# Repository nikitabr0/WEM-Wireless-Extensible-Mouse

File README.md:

# WEM-Wireless-Extensible-Mouse
A computer mouse, that can be connected via USB-C, Bluetooth or a 2.GHz USB dongle. It will have some additional buttons and extra GPIO header(s) for adding more functionality later on.

## Licensing

- **Firmware:** Licensed under the MIT License — see `LICENSE.firmware`.
- **Hardware:** Licensed under CERN-OHL-P-V2 (Permissive) — see https://cern.ch/cern-ohl and `LICENSE.hardware`.

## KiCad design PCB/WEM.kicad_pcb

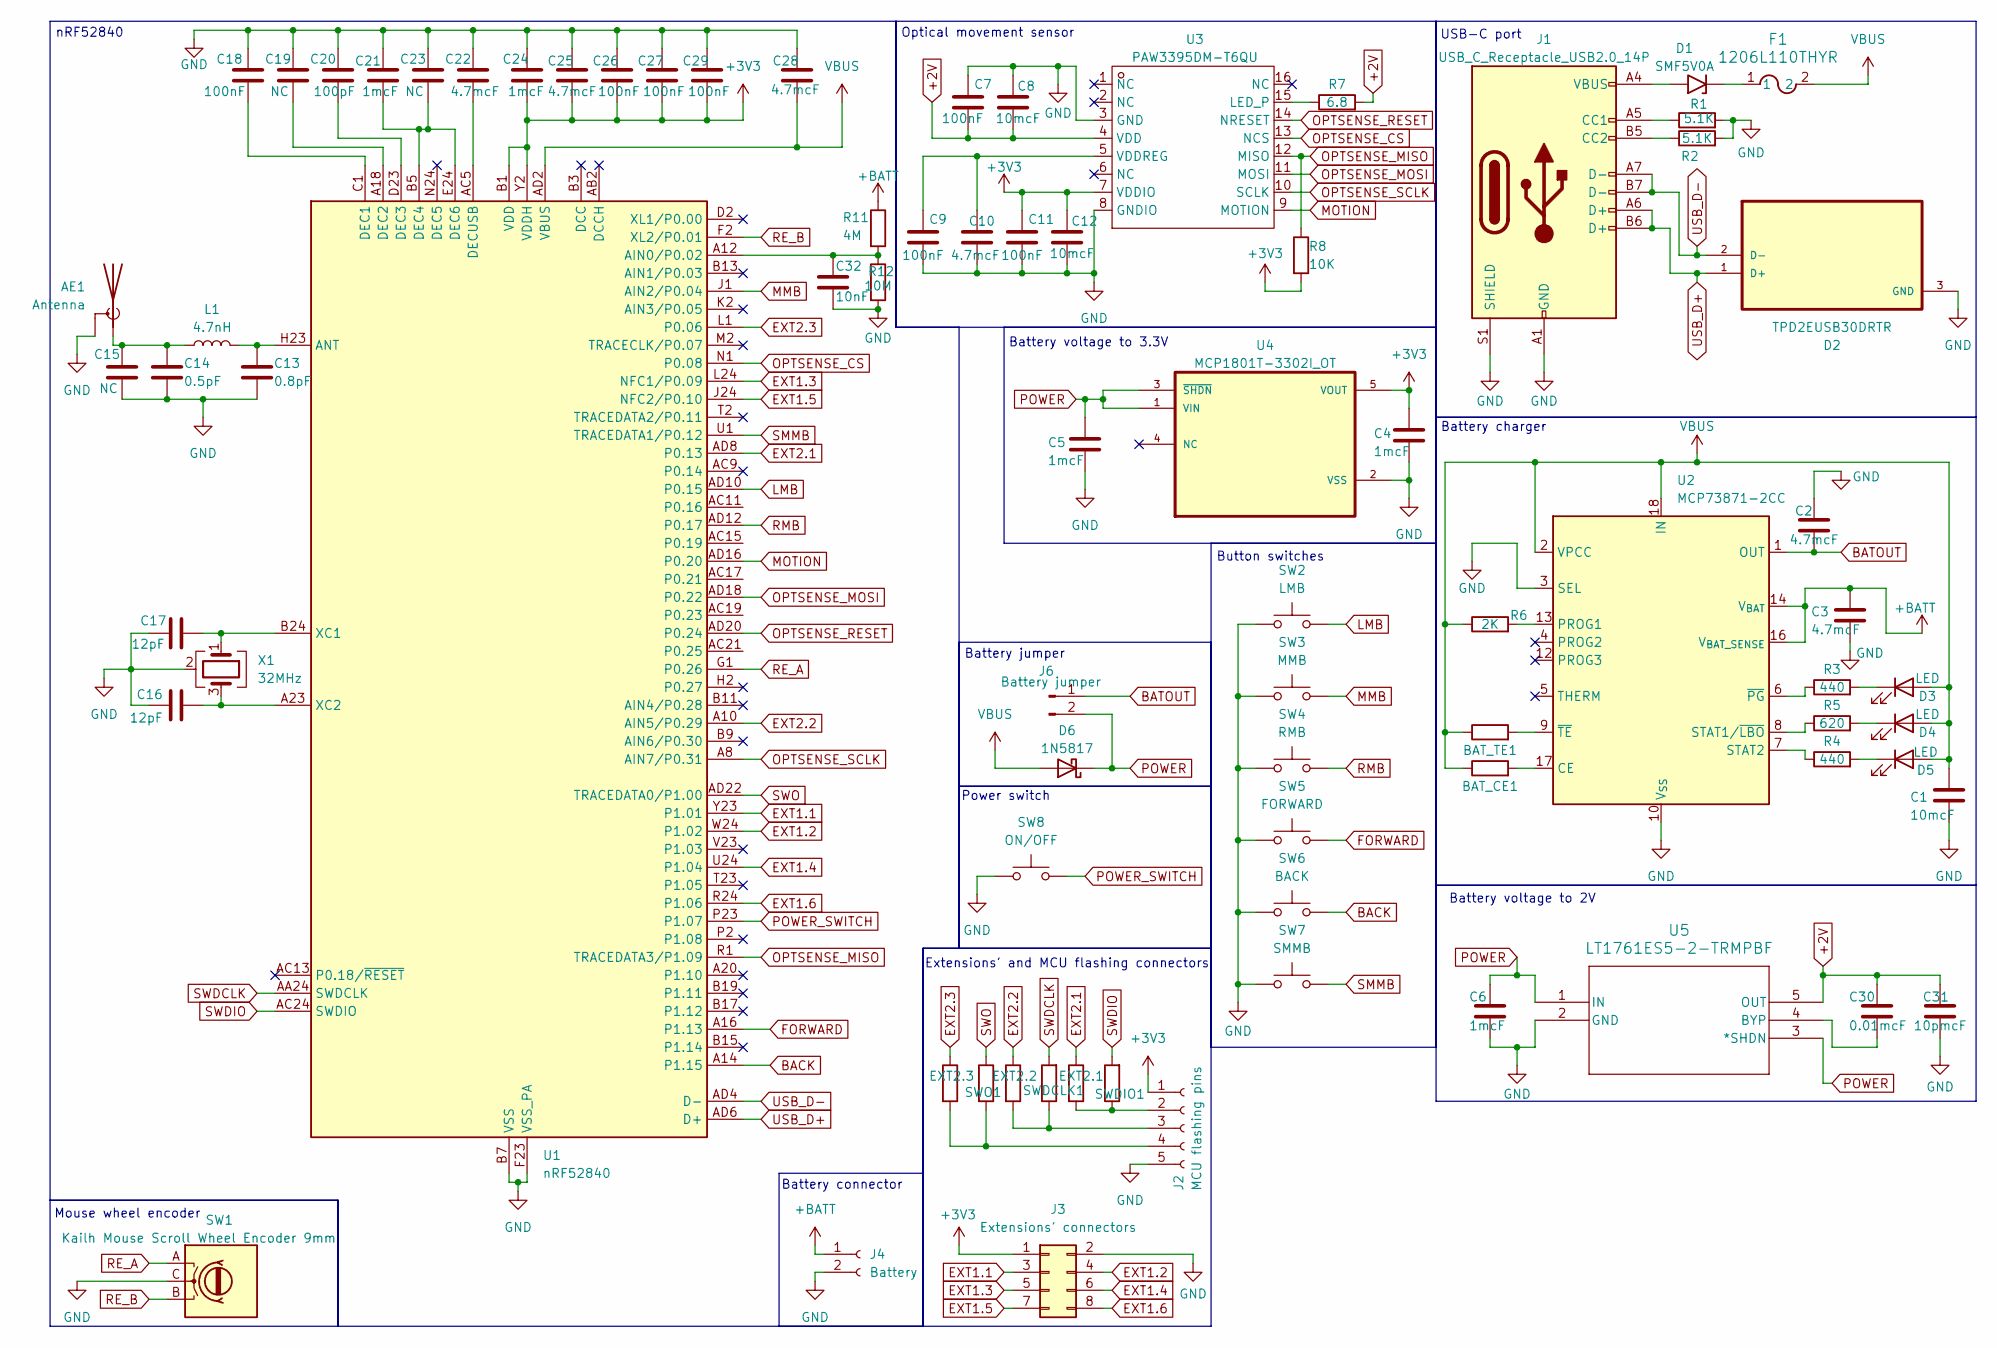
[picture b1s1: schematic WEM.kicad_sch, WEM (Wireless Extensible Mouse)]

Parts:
AE1: Antenna; Texas_SWRA117D_2.4GHz_Right
BAT_CE1: 0; R_0805_2012Metric_Pad1.20x1.40mm_HandSolder
BAT_TE1: 0; R_0805_2012Metric_Pad1.20x1.40mm_HandSolder
C1, C8, C12: 10mcF; C_0805_2012Metric_Pad1.18x1.45mm_HandSolder
C2, C3, C10: 4.7mcF; C_0805_2012Metric_Pad1.18x1.45mm_HandSolder
C4, C5, C6: 1mcF; C_0805_2012Metric_Pad1.18x1.45mm_HandSolder
C7, C9, C11: 100nF; C_0805_2012Metric_Pad1.18x1.45mm_HandSolder
C13: 0.8pF; C_0603_1608Metric_Pad1.08x0.95mm_HandSolder
C14: 0.5pF; C_0603_1608Metric_Pad1.08x0.95mm_HandSolder
C15, C19, C23: NC; C_0603_1608Metric_Pad1.08x0.95mm_HandSolder
C16, C17: 12pF; C_0603_1608Metric_Pad1.08x0.95mm_HandSolder
C18, C26, C27, C29: 100nF; C_0603_1608Metric_Pad1.08x0.95mm_HandSolder
C20: 100pF; C_0603_1608Metric_Pad1.08x0.95mm_HandSolder
C21, C24: 1mcF; C_0603_1608Metric_Pad1.08x0.95mm_HandSolder
C22, C25, C28: 4.7mcF; C_0603_1608Metric_Pad1.08x0.95mm_HandSolder
C30: 0.01mcF; C_0805_2012Metric_Pad1.18x1.45mm_HandSolder
C31: 10pmcF; C_0805_2012Metric_Pad1.18x1.45mm_HandSolder
C32: 10nF; C_0805_2012Metric_Pad1.18x1.45mm_HandSolder
D1: SMF5V0A; D_SMF
D2: TPD2EUSB30DRTR; SOTFL35P100X50-3N
D3, D4, D5: LED; LED_0805_2012Metric_Pad1.15x1.40mm_HandSolder
D6: 1N5817; D_SOD-323F
EXT2.1, EXT2.2, EXT2.3: 0; R_0805_2012Metric_Pad1.20x1.40mm_HandSolder
F1: 1206L110THYR; Fuse_1206_3216Metric_Pad1.42x1.75mm_HandSolder
J1: USB_C_Receptacle_USB2.0_14P; USB_C_Receptacle_GCT_USB4085
J2: MCU flashing pins; PinSocket_1x05_P2.54mm_Vertical
J3: Extensions' connectors; PinSocket_2x04_P2.54mm_Vertical
J4: Battery; JST_XH_B2B-XH-A_1x02_P2.50mm_Vertical
J6: Battery jumper; PinHeader_1x02_P2.54mm_Vertical
L1: 4.7nH; L_0402_1005Metric_Pad0.77x0.64mm_HandSolder
R1, R2: 5.1K; R_0805_2012Metric_Pad1.20x1.40mm_HandSolder
R3, R4: 440; R_0805_2012Metric_Pad1.20x1.40mm_HandSolder
R5: 620; R_0805_2012Metric_Pad1.20x1.40mm_HandSolder
R6: 2K; R_0805_2012Metric_Pad1.20x1.40mm_HandSolder
R7: 6.8; R_0805_2012Metric_Pad1.20x1.40mm_HandSolder
R8: 10K; R_0805_2012Metric_Pad1.20x1.40mm_HandSolder
R11: 4M; R_0805_2012Metric_Pad1.20x1.40mm_HandSolder
R12: 10M; R_0805_2012Metric_Pad1.20x1.40mm_HandSolder
SW1: Kailh Mouse Scroll Wheel Encoder 9mm
SW2: LMB; Kailh MI627301D07
SW3: MMB; Kailh MI627301D07
SW4: RMB; Kailh MI627301D07
SW5: FORWARD; Kailh MI627301D07
SW6: BACK; Kailh MI627301D07
SW7: SMMB; Kailh MI627301D07
SW8: ON/OFF; Kailh MI627301D07
SWDCLK1: 0; R_0805_2012Metric_Pad1.20x1.40mm_HandSolder
SWDIO1: 0; R_0805_2012Metric_Pad1.20x1.40mm_HandSolder
SWO1: 0; R_0805_2012Metric_Pad1.20x1.40mm_HandSolder
U1: nRF52840; Nordic_AQFN-73-1EP_7x7mm_P0.5mm
U2: MCP73871-2CC; QFN-20-1EP_4x4mm_P0.5mm_EP2.5x2.5mm
U3: PAW3395DM-T6QU; DIP-16_PAW3395DM-T6QU; Manufacturer Part PAW3395DM-T6QU; LCSC Part Name PAW3395DM-T6QU
U4: MCP1801T-3302I_OT; SOT-23-5_MC_MCH-M
U5: LT1761ES5-2-TRMPBF; S_5_ADI
X1: 32MHz; Crystal_SMD_2016-4Pin_2.0x1.6mm

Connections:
+2V: C7.2, C8.2, C30.1, C31.1, R7.2, U3.4 (VDD), U5.5 (OUT)
+3V3: C4.1, C11.1, C12.1, C24.2, C25.2, C26.2, C27.2, C29.2, J2.1, J3.1, R8.2, U1.A22 (VDD), U1.AD14 (VDD), U1.AD23 (VDD), U1.B1 (VDD), U1.W1 (VDD), U1.Y2 (VDDH), U3.7 (VDDIO), U4.5 (VOUT)
+BATT: C3.2, J4.1, R11.1, U2.14 (V_{BAT}), U2.15 (V_{BAT}), U2.16 (V_{BAT_SENSE})
BACK: SW6.2, U1.A14 (P1.15)
BATOUT: C2.1, J6.1, U2.1 (OUT), U2.20 (OUT)
EXT1.1: J3.3, U1.Y23 (P1.01)
EXT1.2: J3.4, U1.W24 (P1.02)
EXT1.3: J3.5, U1.L24 (NFC1/P0.09)
EXT1.4: J3.6, U1.U24 (P1.04)
EXT1.5: J3.7, U1.J24 (NFC2/P0.10)
EXT1.6: J3.8, U1.R24 (P1.06)
EXT2.1: EXT2.1.1, U1.AD8 (P0.13)
EXT2.2: EXT2.2.1, U1.A10 (AIN5/P0.29)
EXT2.3: EXT2.3.1, U1.L1 (P0.06)
FORWARD: SW5.2, U1.A16 (P1.13)
GND: AE1.2 (Shield), C1.2, C2.2, C3.1, C4.2, C5.2, C6.2, C7.1, C8.1, C9.2, C10.2, C11.2, C12.2, C13.2, C14.2, C15.2, C16.1, C17.1, C18.1, C19.1, C20.1, C21.1, C22.1, C23.1, C24.1, C25.1, C26.1, C27.1, C28.1, C29.1, C31.2, C32.2, D2.3 (GND), J1.A1 (GND), J1.A12 (GND), J1.B1 (GND), J1.B12 (GND), J1.S1 (SHIELD), J2.5, J3.2, J4.2, R1.2, R2.2, R12.2, SW1.C, SW2.1, SW3.1, SW4.1, SW5.1, SW6.1, SW7.1, SW8.1, U1.B7 (VSS), U1.EP (VSS), U1.F23 (VSS_PA), U2.3 (SEL), U2.10 (V_{SS}), U2.11 (V_{SS}), U2.21 (V_{SS}), U3.3 (GND), U3.8 (GNDIO), U4.2 (VSS), U5.2 (GND), X1.2 (G), X1.4 (G)
LMB: SW2.2, U1.AD10 (P0.15)
MMB: SW3.2, U1.J1 (AIN2/P0.04)
MOTION: U1.AD16 (P0.20), U3.9 (MOTION)
unnamed: AE1.1 (A), C14.1, C15.1, L1.1
unnamed: D1.1 (A1), F1.1
unnamed: D1.2 (A2), J1.A4 (VBUS), J1.A9 (VBUS), J1.B4 (VBUS), J1.B9 (VBUS)
unnamed: D3.1 (K), R3.2
unnamed: D4.1 (K), R5.2
unnamed: D5.1 (K), R4.2
unnamed: J1.A5 (CC1), R1.1
unnamed: J1.B5 (CC2), R2.1
unnamed: EXT2.1.2, J2.2, SWDIO1.1
unnamed: EXT2.2.2, J2.3, SWDCLK1.1
unnamed: EXT2.3.2, J2.4, SWO1.2
unnamed: C32.1, R11.2, R12.1, U1.A12 (AIN0/P0.02)
unnamed: C13.1, L1.2, U1.H23 (ANT)
unnamed: C18.2, U1.C1 (DEC1)
unnamed: C19.2, U1.A18 (DEC2)
unnamed: C20.2, U1.D23 (DEC3)
unnamed: C21.2, C23.2, U1.B5 (DEC4), U1.E24 (DEC6)
unnamed: C22.2, U1.AC5 (DECUSB)
unnamed: C17.2, U1.B24 (XC1), X1.1
unnamed: C16.2, U1.A23 (XC2), X1.3
unnamed: BAT_CE1.2, U2.17 (CE)
unnamed: R6.2, U2.13 (PROG1)
unnamed: R5.1, U2.8 (STAT1/~LBO)
unnamed: R4.1, U2.7 (STAT2)
unnamed: R3.1, U2.6 (~PG)
unnamed: BAT_TE1.2, U2.9 (~TE)
unnamed: R7.1, U3.15 (LED_P)
unnamed: C9.1, C10.1, U3.5 (VDDREG)
unnamed: C30.2, U5.4 (BYP)
OPTSENSE_CS: U1.N1 (P0.08), U3.13 (NCS)
OPTSENSE_MISO: R8.1, U1.R1 (TRACEDATA3/P1.09), U3.12 (MISO)
OPTSENSE_MOSI: U1.AD18 (P0.22), U3.11 (MOSI)
OPTSENSE_RESET: U1.AD20 (P0.24), U3.14 (NRESET)
OPTSENSE_SCLK: U1.A8 (AIN7/P0.31), U3.10 (SCLK)
POWER: C5.1, C6.1, D6.1 (K), J6.2, U4.1 (VIN), U4.3 (~SHDN), U5.1 (IN), U5.3 (*SHDN)
POWER_SWITCH: SW8.2, U1.P23 (P1.07)
RE_A: SW1.A, U1.G1 (P0.26)
RE_B: SW1.B, U1.F2 (XL2/P0.01)
RMB: SW4.2, U1.AD12 (P0.17)
SMMB: SW7.2, U1.U1 (TRACEDATA1/P0.12)
SWDCLK: SWDCLK1.2, U1.AA24 (SWDCLK)
SWDIO: SWDIO1.2, U1.AC24 (SWDIO)
SWO: SWO1.1, U1.AD22 (TRACEDATA0/P1.00)
USB_D+: D2.1 (D+), J1.A6 (D+), J1.B6 (D+), U1.AD6 (D+)
USB_D-: D2.2 (D-), J1.A7 (D-), J1.B7 (D-), U1.AD4 (D-)
VBUS: BAT_CE1.1, BAT_TE1.1, C1.1, C28.2, D3.2 (A), D4.2 (A), D5.2 (A), D6.2 (A), F1.2, R6.1, U1.AD2 (VBUS), U2.2 (VPCC), U2.18 (IN), U2.19 (IN)

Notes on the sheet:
Button switches
Optical movement sensor
Battery voltage to 2V
Power switch
USB-C port
Battery connector
Battery voltage to 3.3V
Battery charger
Extensions' and MCU flashing connectors
Battery jumper
nRF52840
Mouse wheel encoder

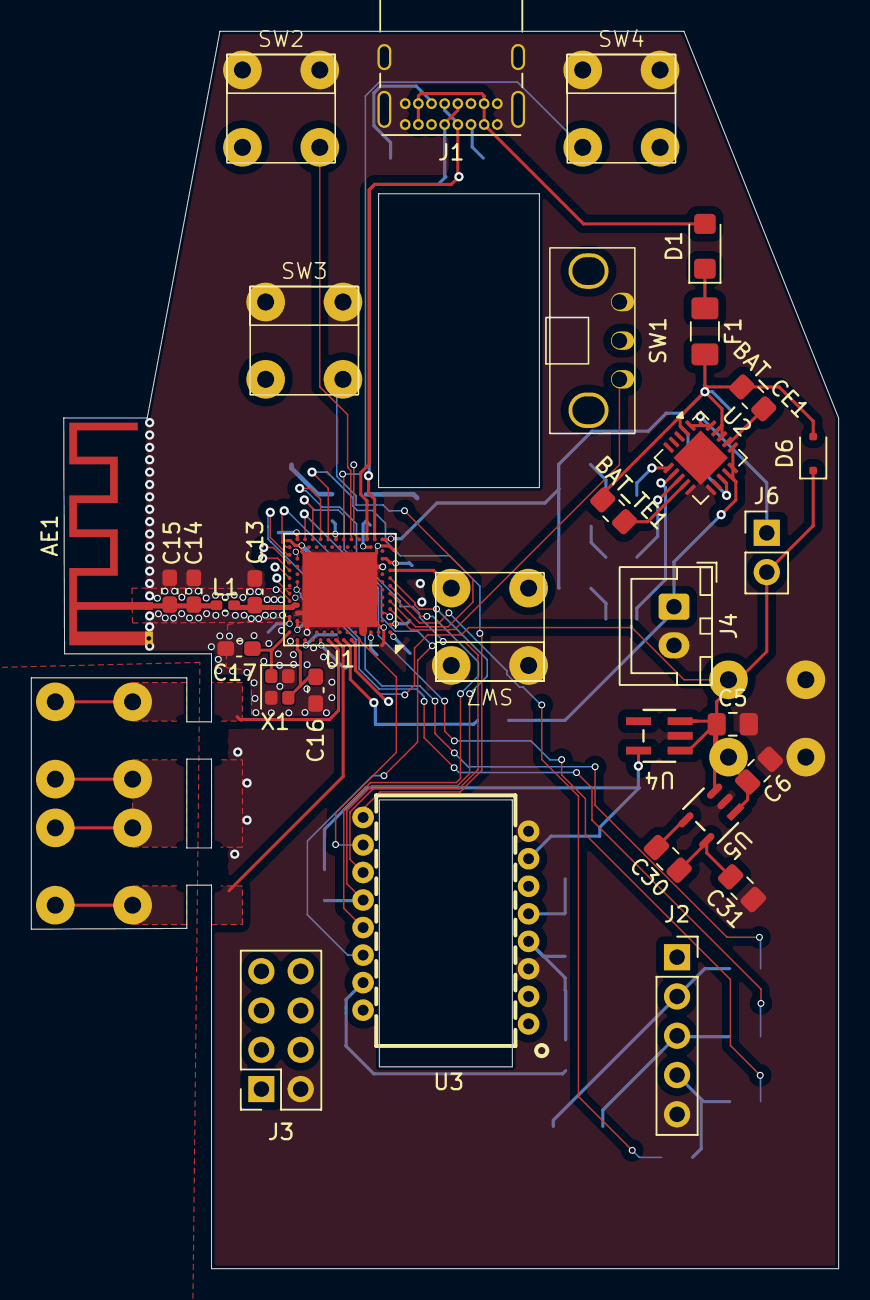
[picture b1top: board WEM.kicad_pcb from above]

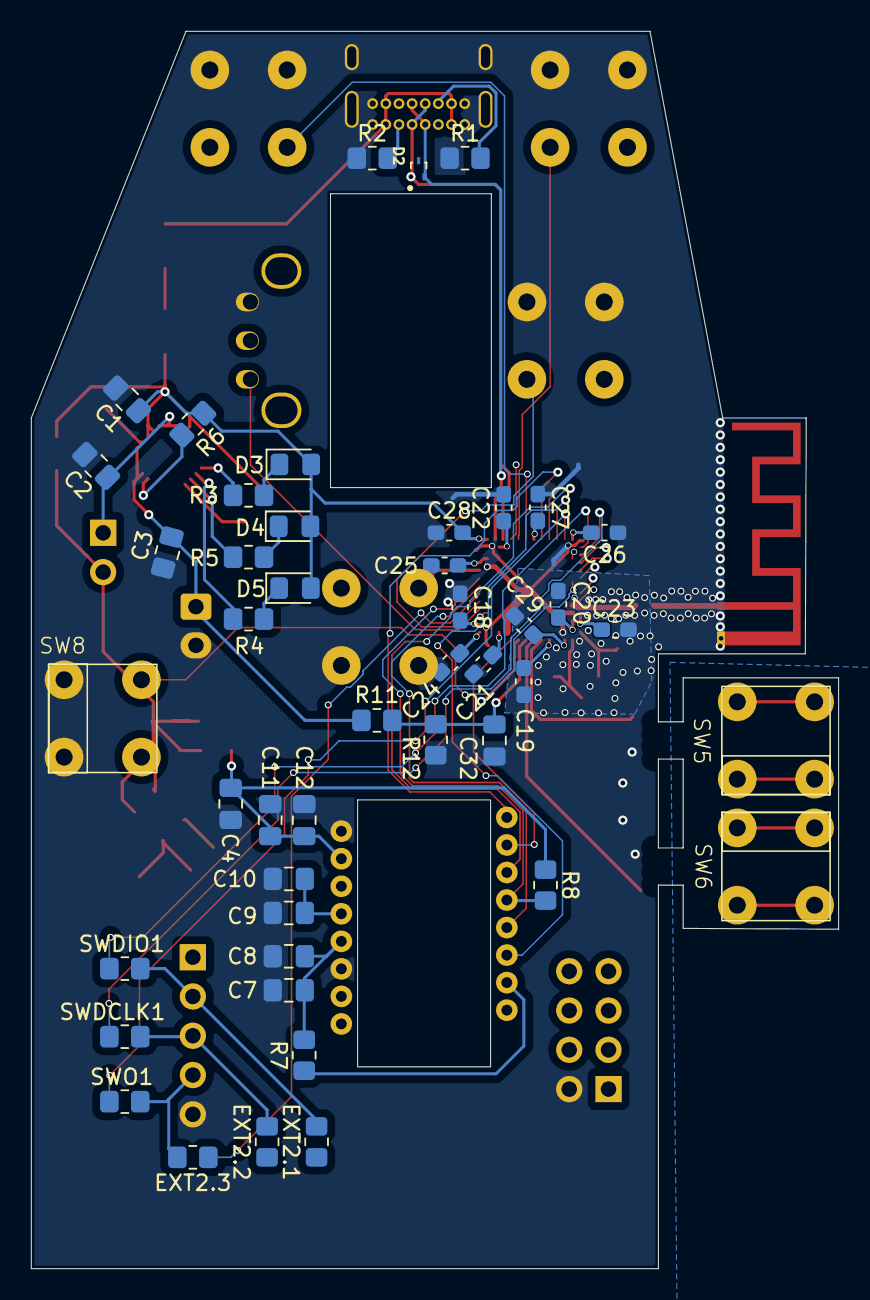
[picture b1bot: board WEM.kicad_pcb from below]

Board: 2 copper layers, 52.2 x 80.0 mm, 78 parts (46 on the bottom side), 65 nets.

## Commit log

2026-01-17 Working environment, licences, MCU, firmware
2026-01-18 Started schematic design
2026-01-22 Voltage regulators and schematic progress
2026-01-23 Mouse wheel encoder amd more work on schematics
2026-01-24 More schematics
2026-01-24 Clearing up the mess
2026-01-25 Finished schematics
2026-01-30 Schematics modifications and firmware
2026-02-14 Started PCB routing
2026-03-15 Continued routing. It's hopeless
